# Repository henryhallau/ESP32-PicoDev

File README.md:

# ESP32-PicoDev 1.0
A small project, mainly built for creating a prototype for my Smartwatch (more coming on that later).
It was created in KiCad, and this is the format of the project files.

A rendered version of the board

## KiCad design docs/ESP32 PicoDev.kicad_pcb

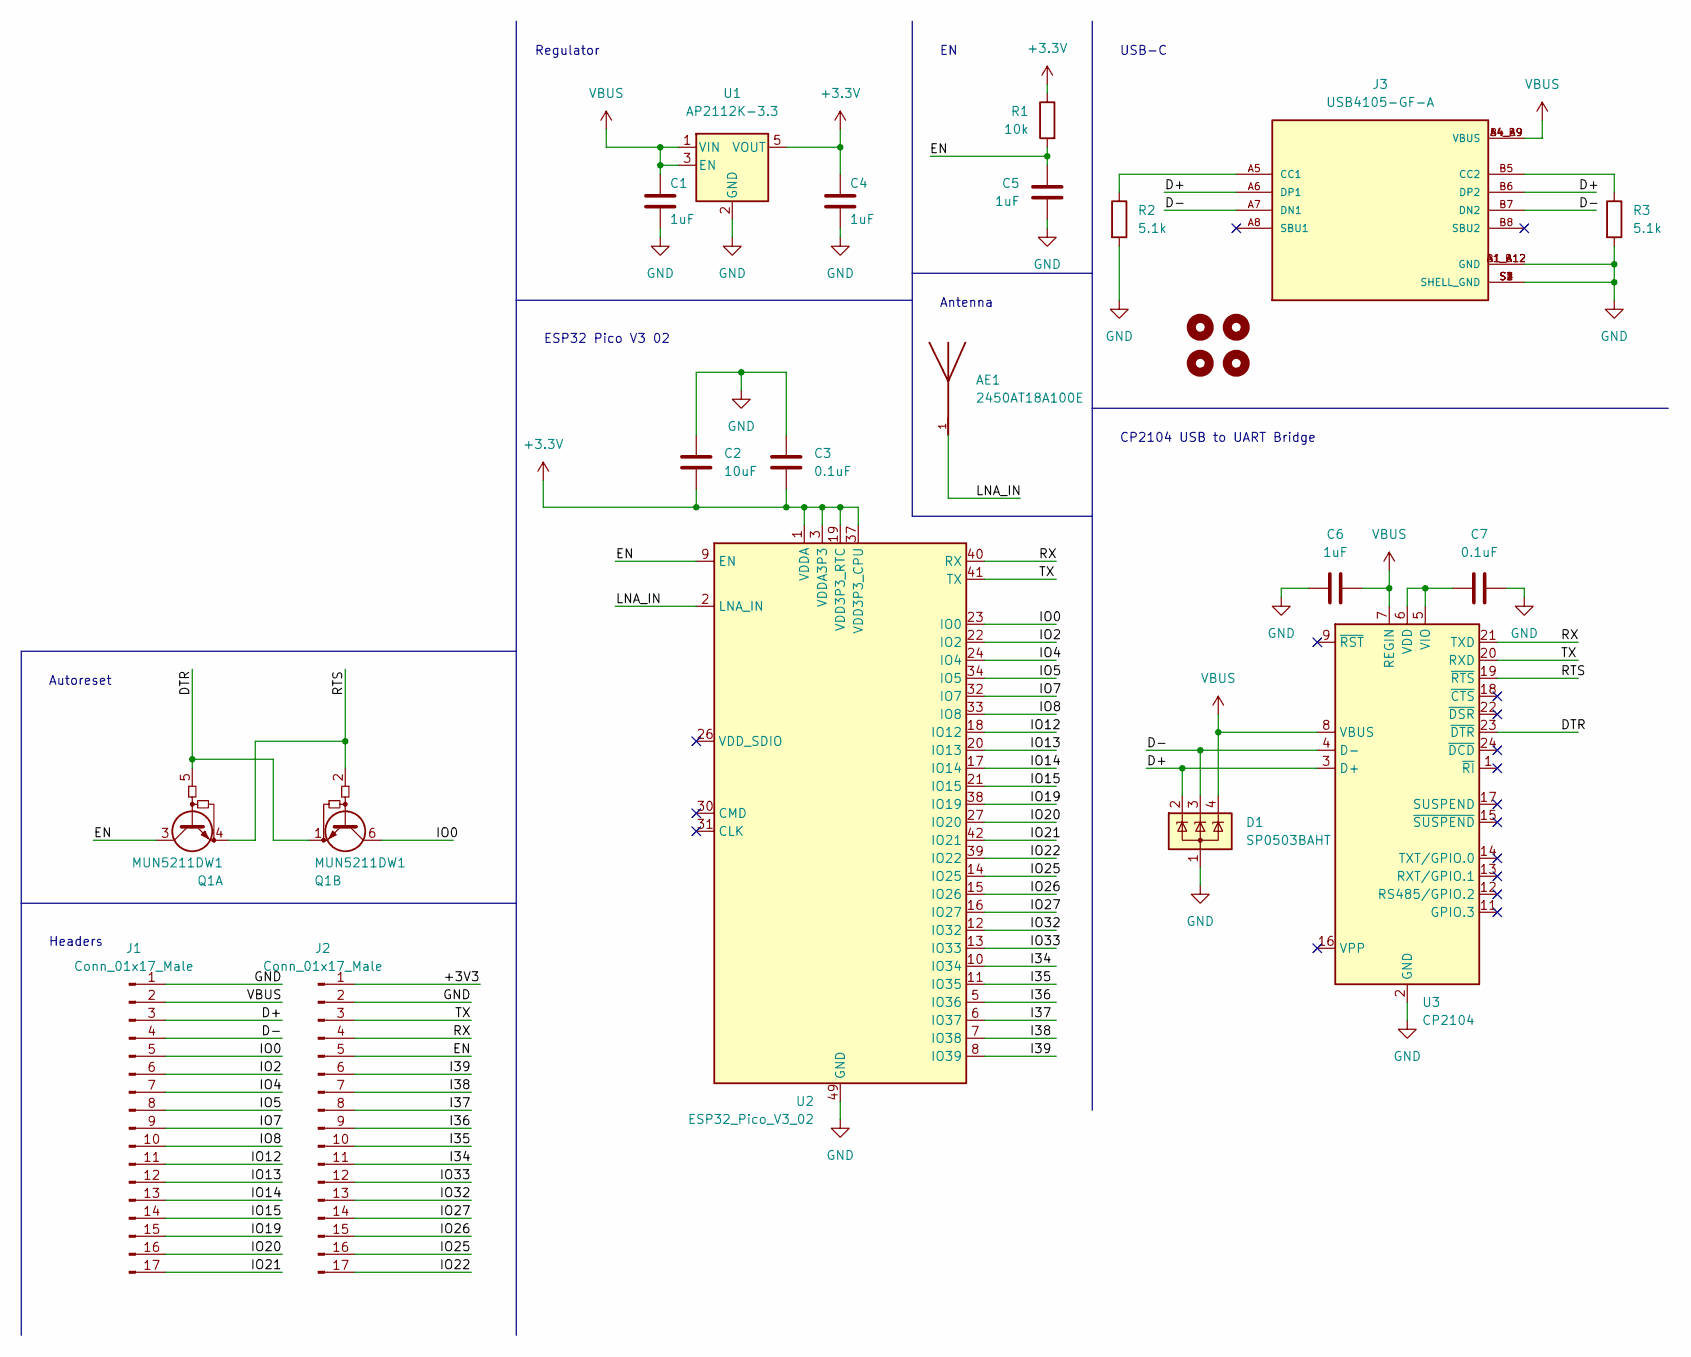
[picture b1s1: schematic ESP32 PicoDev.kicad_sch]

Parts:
AE1: 2450AT18A100E; ANTC3216X140N; PARTREV 1.3
C1, C4, C5, C6: 1uF; C_0603_1608Metric
C2: 10uF; C_0603_1608Metric
C3, C7: 0.1uF; C_0603_1608Metric
D1: SP0503BAHT; SOT-143
H1, H2, H3, H4: MountingHole; MountingHole2.54
J1, J2: Conn_01x17_Male; PinHeader_1x17_P2.54mm_Vertical
J3: USB4105-GF-A; GCT_USB4105-GF-A; PARTREV A3
Q1: MUN5211DW1; SOT-363_SC-70-6
R1: 10k; R_0603_1608Metric
R2, R3: 5.1k; R_0603_1608Metric
U1: AP2112K-3.3; SOT-23-5
U2: ESP32_Pico_V3_02; QFN-48-1EP_7x7mm_P0.5mm_EP5.3x5.3mm
U3: CP2104; QFN-24-1EP_4x4mm_P0.5mm_EP2.6x2.6mm

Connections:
/D+: D1.2 (K), J1.3, J3.A6 (DP1), J3.B6 (DP2), U3.3 (D+)
/D-: D1.3 (K), J1.4, J3.A7 (DN1), J3.B7 (DN2), U3.4 (D-)
/DTR: Q1.1 (E2), Q1.5 (B1), U3.23 (~DTR)
/EN: C5.1, J2.5, Q1.3 (C1), R1.2, U2.9 (EN)
/I34: J2.11, U2.10 (IO34)
/I35: J2.10, U2.11 (IO35)
/I36: J2.9, U2.5 (IO36)
/I37: J2.8, U2.6 (IO37)
/I38: J2.7, U2.7 (IO38)
/I39: J2.6, U2.8 (IO39)
/IO0: J1.5, Q1.6 (C2), U2.23 (IO0)
/IO2: J1.6, U2.22 (IO2)
/IO4: J1.7, U2.24 (IO4)
/IO5: J1.8, U2.34 (IO5)
/IO7: J1.9, U2.32 (IO7)
/IO8: J1.10, U2.33 (IO8)
/IO12: J1.11, U2.18 (IO12)
/IO13: J1.12, U2.20 (IO13)
/IO14: J1.13, U2.17 (IO14)
/IO15: J1.14, U2.21 (IO15)
/IO19: J1.15, U2.38 (IO19)
/IO20: J1.16, U2.27 (IO20)
/IO21: J1.17, U2.42 (IO21)
/IO22: J2.17, U2.39 (IO22)
/IO25: J2.16, U2.14 (IO25)
/IO26: J2.15, U2.15 (IO26)
/IO27: J2.14, U2.16 (IO27)
/IO32: J2.13, U2.12 (IO32)
/IO33: J2.12, U2.13 (IO33)
/LNA_IN: AE1.1, U2.2 (LNA_IN)
/RTS: Q1.2 (B2), Q1.4 (E1), U3.19 (~RTS)
/RX: J2.4, U2.40 (RX), U3.21 (TXD)
/TX: J2.3, U2.41 (TX), U3.20 (RXD)
GND: C1.2, C2.1, C3.1, C4.2, C5.2, C6.1, C7.2, D1.1 (A), J1.1, J2.2, J3.A1_B12 (GND), J3.B1_A12 (GND), J3.S1 (SHELL_GND), J3.S2 (SHELL_GND), J3.S3 (SHELL_GND), J3.S4 (SHELL_GND), R2.2, R3.2, U1.2 (GND), U2.49 (GND), U3.2 (GND), U3.25 (GND)
unnamed: C7.1, U3.5 (VIO), U3.6 (VDD)
unnamed: J3.A5 (CC1), R2.1
unnamed: J3.B5 (CC2), R3.1
VBUS: C1.1, C6.2, D1.4 (K), J1.2, J3.A4_B9 (VBUS), J3.B4_A9 (VBUS), U1.1 (VIN), U1.3 (EN), U3.7 (REGIN), U3.8 (VBUS)

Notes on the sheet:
CP2104 USB to UART Bridge
Antenna
Regulator
USB-C
Headers
ESP32 Pico V3 02
Autoreset

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
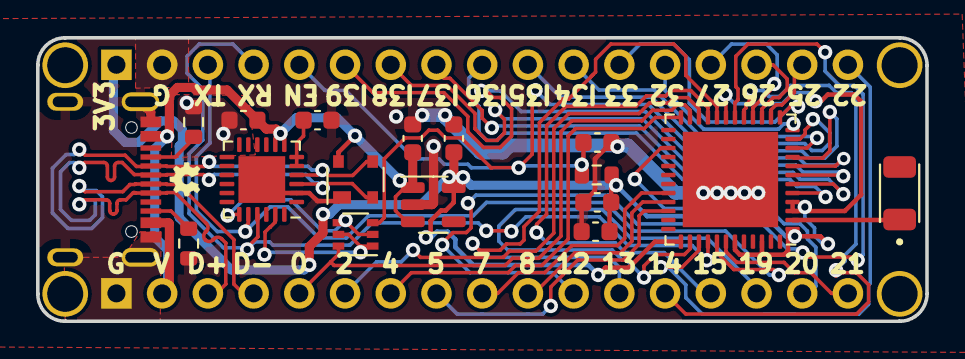
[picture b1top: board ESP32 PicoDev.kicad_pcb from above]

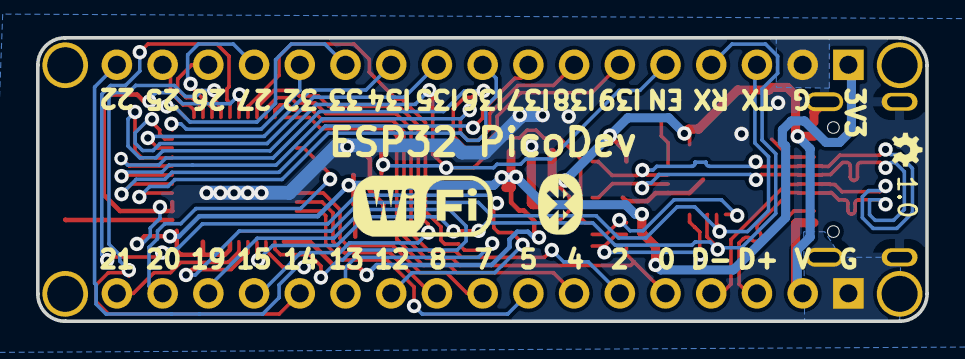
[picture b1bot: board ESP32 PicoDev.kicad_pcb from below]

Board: 2 copper layers, 49.4 x 15.7 mm, 23 parts (2 on the bottom side), 39 nets.
